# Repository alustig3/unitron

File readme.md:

# Unitron

<a href="https://certification.oshwa.org/us002571.html">
</img>
</a>

Unitron is a kitchen tool for working with important cooking units -- time, space, and mass -- using tactually-pleasing switches, knobs, and buttons, non-intrusive beeps, and exciting lights.

Unitron allows you to convert between common volume units (cups, ounces, tablespoons, teaspoons and milliliters). It can also convert from volume to mass (and vice-versa), taking into account the density of common cooking ingredients. This makes measuring ingredients for volume-based recipes with a kitchen scale a breeze. It also functions as a handy countdown timer!

Watch the demo video [here](https://vimeo.com/719658219).

Unitron was developed by Andy Lustig.

## Build Guide

### BOM

| Qty | Reference     | Description              | Value/MPN                                                                                                                                            |
| --- | ------------- | ------------------------ | ---------------------------------------------------------------------------------------------------------------------------------------------------- |
| 1   | BT2           | Battery Connector        | [2468](https://www.digikey.com/product-detail/en/keystone-electronics/2466/36-2466-ND/303815)                                                        |
| 1   | C1            | 0805 Capacitor           | 1µF                                                                                                                                                  |
| 1   | C2            | 0805 Capacitor           | 100nF                                                                                                                                                |
| 1   | C3            | 0805 Capacitor           | 10µF                                                                                                                                                 |
| 6   | D1-6          | Addressable RGB LED      | [WS2812B](https://cdn-shop.adafruit.com/datasheets/WS2812B.pdf)                                                                                      |
| 1   | D7            | Diode                    | [SM5817PL-TP](https://www.digikey.com/en/products/detail/micro-commercial-co/SM5817PL-TP/1793251)                                                    |
| 2   | D8, D9        | 0805 Indicator LED       | Red and Yellow                                                                                                                                       |
| 4   | H1-4          | Threaded Standoff        | [4207](https://www.adafruit.com/product/4207)                                                                                                        |
| 2   | J1, J3        | 1x8 male header          | [TSM-108-01-T-SV](https://www.digikey.com/en/products/detail/samtec-inc/TSM-108-01-T-SV/6679033)                                                     |
| 2   | J2, J4        | 1x8 female header        | [SSW-108-01-T-S](https://www.digikey.com/en/products/detail/samtec-inc/SSW-108-01-T-S/1112297)                                                       |
| 1   | LS1           | Buzzer                   | [PK-11N40PQ](https://www.digikey.com/en/products/detail/mallory-sonalert-products-inc/PK-11N40PQ/4996072?s=N4IgTCBcDaICwFYAcBaAjAZjmFA7AJiALoC%2BQA) |
| 21  | R1-18, R22-24 | 0805 Resistor            | 10KΩ                                                                                                                                                 |
| 3   | R19, R20, R21 | 0805 Resistor            | 2KΩ                                                                                                                                                  |
| 14  | S1-14         | Mechanical Key Switch    | [Gateron green](https://www.amazon.com/Gateron-KS-9-Mechanical-Type-Switch/dp/B07X3TH4DS?th=1)                                                       |
| 1   | SW1           | Small Toggle             | [B12AP](https://www.digikey.com/en/products/detail/nkk-switches/B12AP/379099)                                                                        |
| 1   | SW2           | Big Toggle               | [M2012EA2W13](https://www.digikey.com/en/products/detail/nkk-switches/M2012EA2W13/4509655)                                                           |
| 1   | SW3           | Rotary Encoder           | [PEC11R-4215F-S0024](https://www.digikey.com/en/products/detail/bourns-inc/PEC11R-4215F-S0024/4499665)                                               |
| 2   | U1, U2        | Yellow 4-Digit Display   | [LTC-4727JS](https://www.digikey.com/products/en?keywords=LTC-4727JS)                                                                                |
| 2   | U6, U7        | Red 4-Digit Display      | [LTC-4727JR](https://www.digikey.com/products/en?keywords=160-1551-5-nd)                                                                             |
| 2   | U3, U8        | 7-Segment Display Driver | [AS1115-BSST](https://www.digikey.com/products/en?keywords=AS1115-BSSTCT-ND)                                                                         |
| 1   | U4            | QT Py RP2040             | [4900](https://www.adafruit.com/product/4900)                                                                                                        |
| 1   | U5            | Battery Charging IC      | [MCP73831](https://www.digikey.com/en/products/detail/microchip-technology/MCP73831T-2ATI-OT/964303)                                                 |

<div style="">
  
</div>

### Additional Components
- A rechargeable 3.7V lithium polymer (LiPo) [battery](https://www.adafruit.com/product/1578)
- Threaded mounting [magnets](https://www.kjmagnetics.com/proddetail.asp?prod=MM-C-10)
- A satisfyingly knurled [metal knob](https://www.digikey.com/en/products/detail/kilo-international/OEDNI-63-4-7/5970335).
- Keycaps from WASD keycaps:
  - [number pad keycap set](https://www.wasdkeyboards.com/17-key-cherry-mx-number-pad-keycap-set.html) for the numbers (black, large font)
  - The number pad set comes with a 1x2 "0" keycap, but we want a [custom 1x1 "0" keycap](https://www.wasdkeyboards.com/custom-text-cherry-mx-keycaps.html) (R1 1x1, 26 font, center-center alignment)
  - [R1 1x1 keycaps](https://www.wasdkeyboards.com/row-1-size-1x1-cherry-mx-keycap.html) (sky blue, green, and orange)
- [Relegendable keycaps](https://www.adafruit.com/product/5039) are a good less expensive alternative.

## User Guide

### Component Diagram

### Turning it on!

The first step to using your Unitron is to turn it on with the smaller, right-most [On/Off switch](#diagram). When Unitron is on, the [LED panel](#diagram) and the red [Power indicator light](#diagram) will be lit up. Turn it off to save power.

### Switching Modes

Unitron has a [countdown timer mode](#timer) and [converter mode](#convert).
To **switch to modes**, click the [blue Mode button](#diagram).
Unitron will startup in the `start_mode` specified in your `settings.py` file (see [Modifying Unitron functionality](#modify)).
If the [blue Mode button](#diagram) is pressed down when turning on Unitron, it will startup in the opposite mode. 

### Countdown timer mode
To **set the timer**, use the number keys. To specify minutes and seconds, you can use the decimal key, e.g. 20.30 corresponds to 20 minutes and 30 seconds, while 20 corresponds to 20 seconds.

To **start** the timer, flip the [Toggle switch](#diagram). To **pause** the timer, flip the [Toggle switch](#diagram) again. The top, red row of the LED panel shows the time remaining, and the bottom orange row shows the original time requested.

To **clear** the timer, pause the timer (if necessary), then push the green [Clear button](#diagram).

As the timer counts down to 0, a bar of [Timer lights](#diagram) will progressively light up. When the timer reaches 0, it will beep three times.

### Converter mode
Unitron converts **from blinking to solid units** in the [Unit light](#diagram) row.

You can **enter the amount** of the **blinking "from"** units with the number keys. This will be shown in the [LED panel](#diagram). The corresponding amount in the **solid "to"** units will be shown in the other row of the [LED panel](#diagram).

You can **change units** using the [Knob](#diagram). Turning the knob changes the **blinking "from" units**. Turning the knob while holding it down changes the **solid "to" units**.

You can **swap** the "from" and "to" units with the [Toggle switch](#diagram).  If you find it difficult to hold down the Knob while turning it, you can use the Toggle switch to swap, turn the knob, then flip the Toggle switch back.

Conversions between volume and mass require knowing the density of the ingredient. You can **specify cooking ingredients** by holding down the orange [Ingredient button](#diagram) while turning the [Knob](#diagram). Note that the ingredient button only functions when the two units selected are mass and volume -- ingredient type does not matter when converting from mass to mass or volume to volume.

### Charging

Unitron is rechargeable. To charge it, plug a USB C cable into the [USB port](#diagram) at the top. The yellow charging indicator will be on while charging and will turn off when the battery is full.

### Placement

The back of Unitron has four strong magnets. It is meant to be placed on a metallic refrigerator.

###  Modifying Unitron functionality

Unitron uses [CircuitPython](https://learn.adafruit.com/welcome-to-circuitpython). 
You can modify the code it is running by connecting it to your computer via the [USB C port](#diagram) and mounting it as a disk drive.
Basic settings can be adjusted by editing the `settings.py` file.

**Change the mode that Unitron starts up in when turned on** by editing `start_mode`.

**Adjust the number of beeps** for when the timer expires by editing `beep_num`.

To **add new ingredients** to Unitron, modify `ingredients`. Specify the density in grams per teaspoon. You can try to measure these densities yourself, or you can trust the internet. Here's one [site](https://www.howmany.wiki/vw/) with information.

Make sure to **eject** Unitron before disconnecting.

### Updating 
#### CircuitPython
Connect Unitron to a computer via the [USB C port](#diagram).
To enter bootloader mode, hold down the `BOOT` button, and while continuing to hold it, press and release the `RST` button. Continue to hold the boot select button until the bootloader drive appears on your computer as `RPI-RP2`.
Download `adafruit-circuitpython-adafruit_qtpy_rp2040-en_US-9.0.4.uf2` file from the [release page](https://github.com/alustig3/unitron/releases) and drag it onto the bootloader drive. The `RPI-RP2` drive will disappear, and a new drive called `CIRCUITPY` will appear.

If you have trouble, take a look at the official CirtcuitPython installation instructions [here](https://learn.adafruit.com/welcome-to-circuitpython/installing-circuitpython).

#### Unitron Software
Connect Unitron to a computer via the [USB C port](#diagram).
It should appear as `CIRCUITPY`.
Download the latest software [release](https://github.com/alustig3/unitron/releases).
Unzip the download and copy the files onto the `CIRCUITPY` drive.

## License
[CERN Open Hardware Licence Version 2 - Permissive](https://github.com/alustig3/unitron/blob/main/LICENSE.txt)

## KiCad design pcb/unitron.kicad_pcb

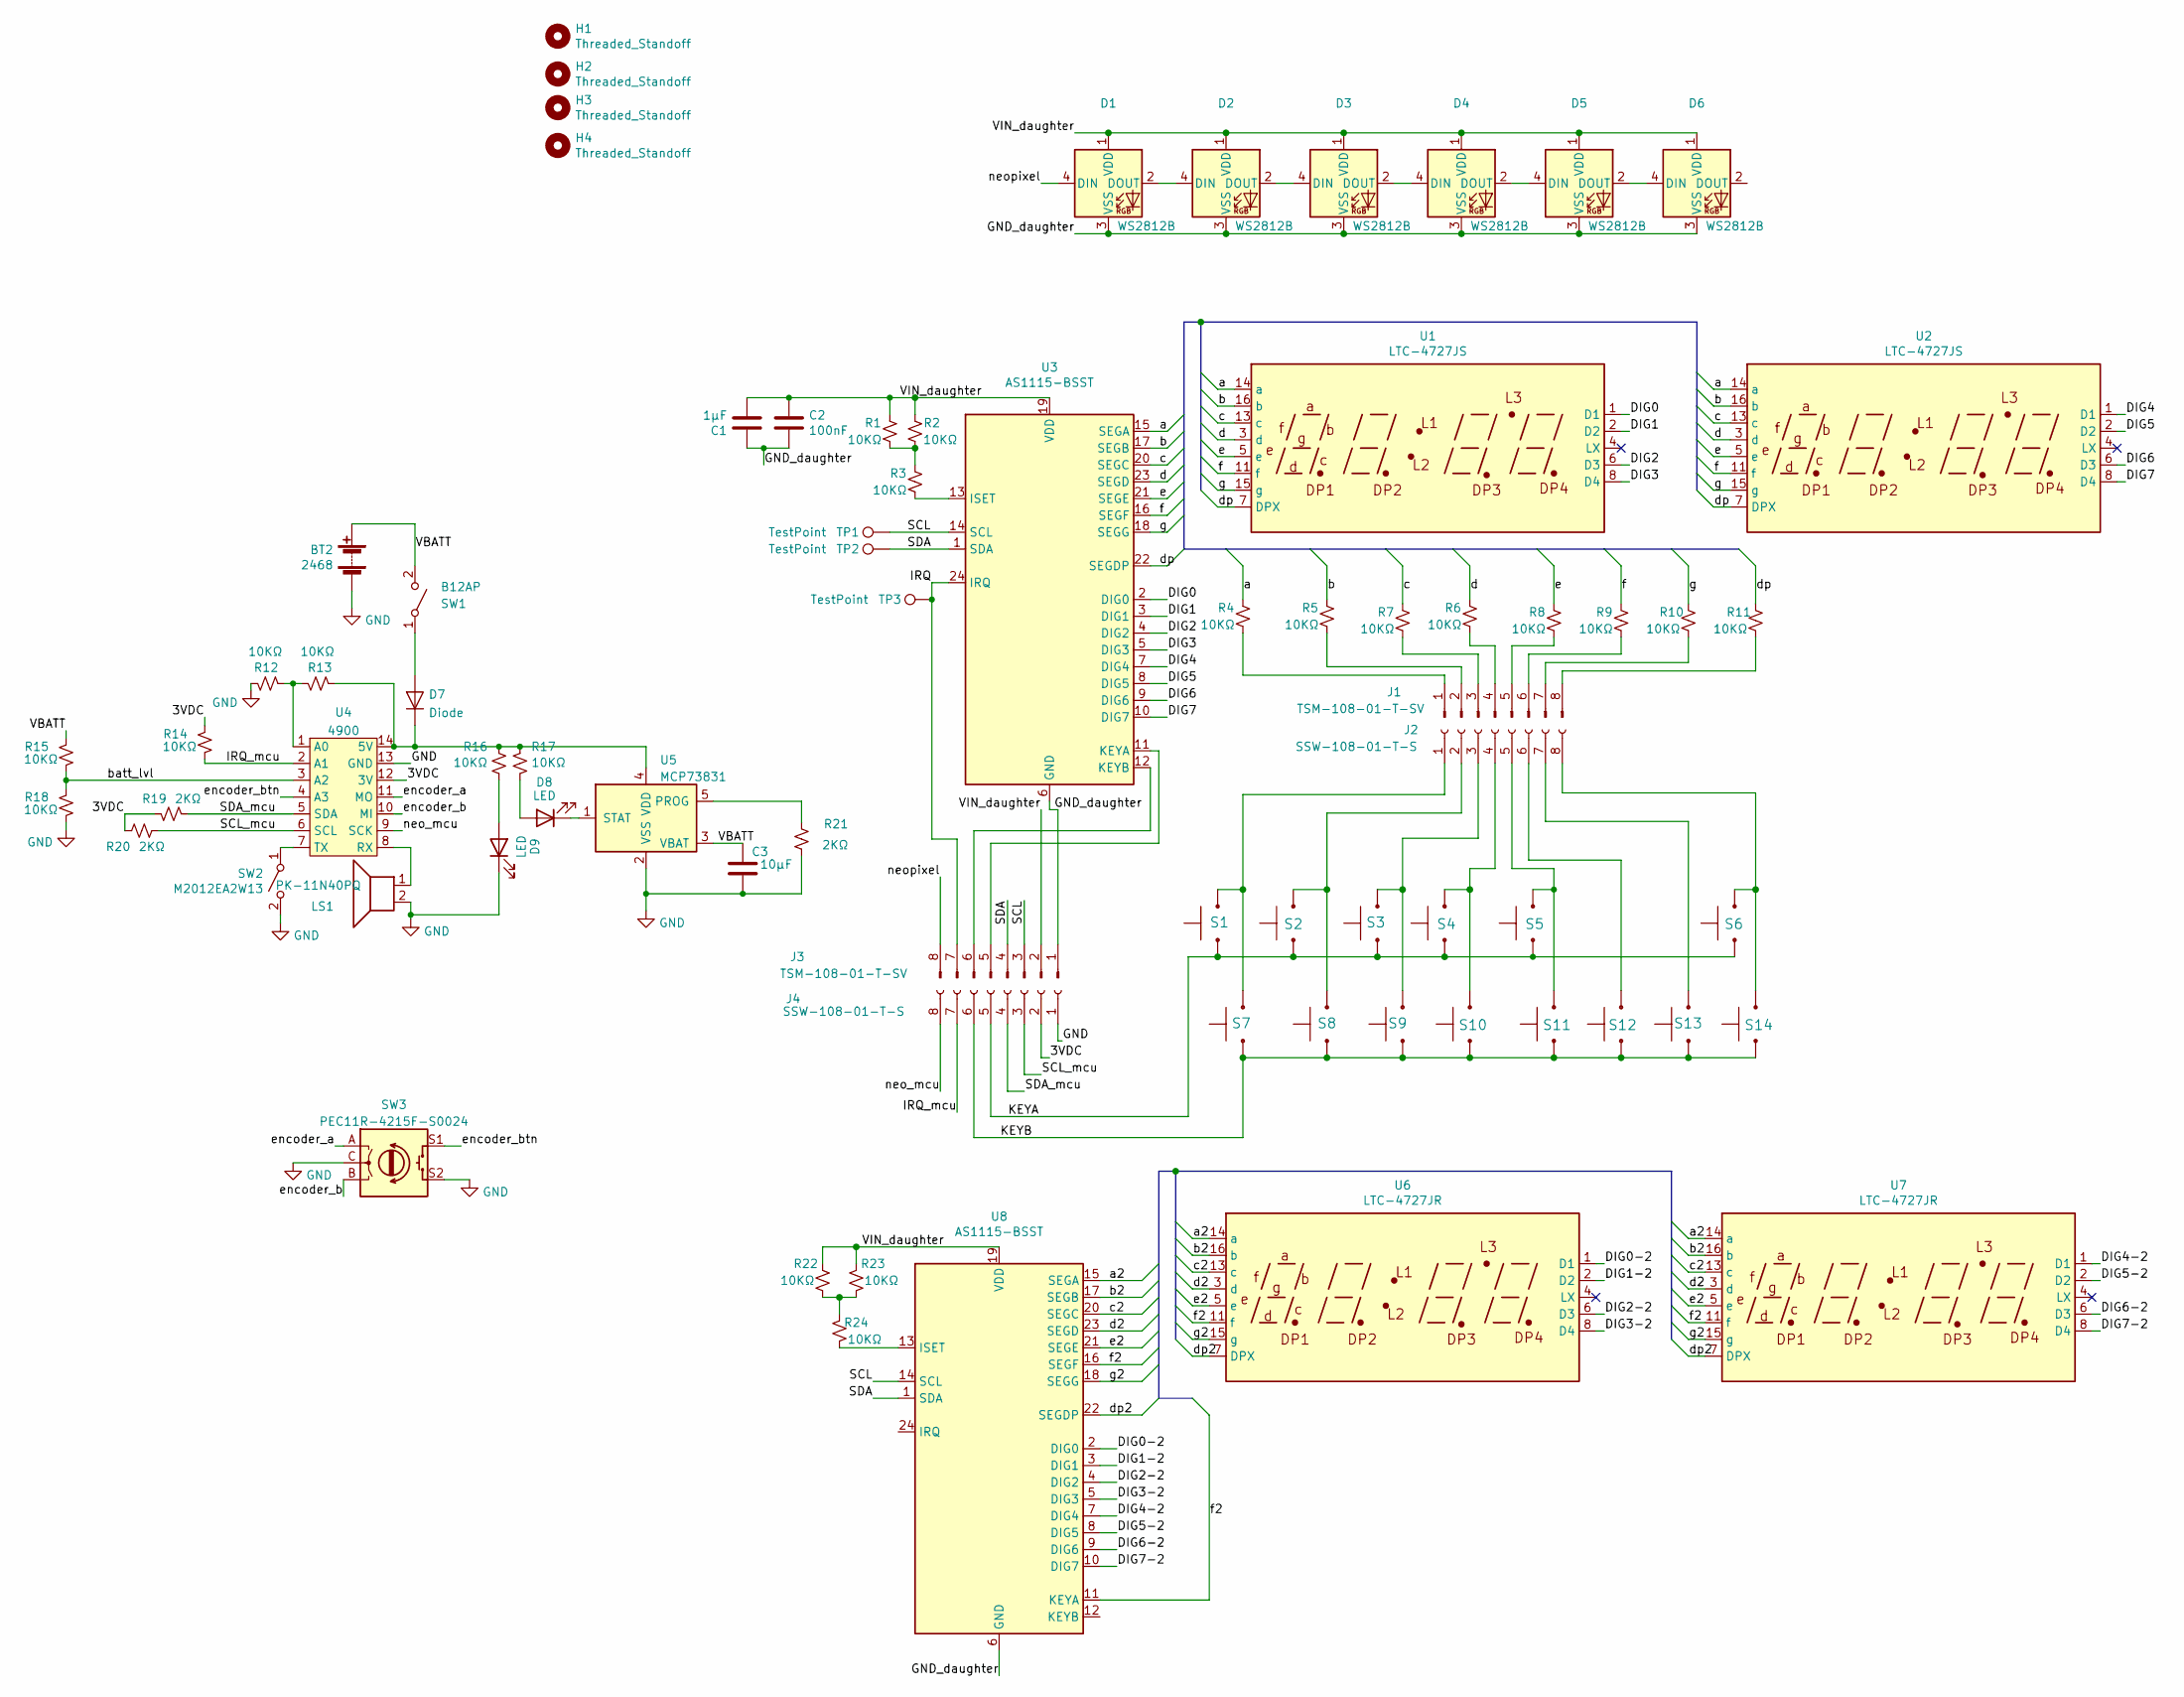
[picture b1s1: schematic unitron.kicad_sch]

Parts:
BT2: 2468; JST_PH_S2B-PH-SM4-TB_1x02-1MP_P2.00mm_Horizontal
C1: 1µF; C_0805_2012Metric
C2: 100nF; C_0805_2012Metric
C3: 10µF; C_0805_2012Metric
D1, D2, D3, D4, D5, D6: WS2812B; LED_WS2812B_PLCC4_5.0x5.0mm_P3.2mm
D7: Diode; D_SOD-123F
D8, D9: LED; LED_0805_2012Metric
H1, H2, H3, H4: Threaded_Standoff; standoff_nut
J1, J3: TSM-108-01-T-SV; PinSocket_1x08_P2.54mm_Vertical_SMD_Pin1Right
J2, J4: SSW-108-01-T-S; PinHeader_1x08_P2.54mm_Vertical
LS1: PK-11N40PQ; Buzzer_12x9.5RM7.6
R1, R2, R3, R4, R5, R6, R7, R8, R9, R10, R11, R12, R13, R14, R15, R16, R17, R18, R22, R23, R24: 10KΩ; R_0805_2012Metric
R19, R20, R21: 2KΩ; R_0805_2012Metric
S1, S2, S3, S4, S5, S6, S7, S8, S9, S10, S11, S12, S13, S14: Gateron green; SW_Cherry_MX_1.00u_PCB
SW1: B12AP; switch_toggle
SW2: M2012EA2W13; switch_nkk_reinforced_pc_pin
SW3: PEC11R-4215F-S0024; encoder_PEC11R
TP1, TP2, TP3: TestPoint; TestPoint_Pad_1.0x1.0mm
U1, U2: LTC-4727JS; LTC-4727
U3, U8: AS1115-BSST; QSOP-24_3.9x8.7mm_P0.635mm
U4: 4900; QT_Py
U5: MCP73831; SOT-23-5
U6, U7: LTC-4727JR; LTC-4727

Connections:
/3VDC: J4.2, R14.1, R19.2, R20.2, U4.12 (3V)
/DIG0: U1.1 (D1), U3.2 (DIG0)
/DIG0-2: U6.1 (D1), U8.2 (DIG0)
/DIG1: U1.2 (D2), U3.3 (DIG1)
/DIG1-2: U6.2 (D2), U8.3 (DIG1)
/DIG2: U1.6 (D3), U3.4 (DIG2)
/DIG2-2: U6.6 (D3), U8.4 (DIG2)
/DIG3: U1.8 (D4), U3.5 (DIG3)
/DIG3-2: U6.8 (D4), U8.5 (DIG3)
/DIG4: U2.1 (D1), U3.7 (DIG4)
/DIG4-2: U7.1 (D1), U8.7 (DIG4)
/DIG5: U2.2 (D2), U3.8 (DIG5)
/DIG5-2: U7.2 (D2), U8.8 (DIG5)
/DIG6: U2.6 (D3), U3.9 (DIG6)
/DIG6-2: U7.6 (D3), U8.9 (DIG6)
/DIG7: U2.8 (D4), U3.10 (DIG7)
/DIG7-2: U7.8 (D4), U8.10 (DIG7)
/GND_daughter: C1.1, C2.2, D1.3 (VSS), D2.3 (VSS), D3.3 (VSS), D4.3 (VSS), D5.3 (VSS), D6.3 (VSS), J3.1, U3.6 (GND), U8.6 (GND)
/IRQ: J3.7, TP3.1, U3.24 (IRQ)
/IRQ_mcu: J4.7, R14.2, U4.2 (A1)
/KEYA: J4.5, S1.1, S2.1, S3.1, S4.1, S5.1, S6.1
/KEYB: J4.6, S7.1, S8.1, S9.1, S10.1, S11.1, S12.1, S13.1, S14.1
/SCL: J3.3, TP1.1, U3.14 (SCL), U8.14 (SCL)
/SCL_mcu: J4.3, R20.1, U4.6 (SCL)
/SDA: J3.4, TP2.1, U3.1 (SDA), U8.1 (SDA)
/SDA_mcu: J4.4, R19.1, U4.5 (SDA)
/VBATT: BT2.1 (+), C3.1, R15.1, SW1.2 (B), U5.3 (VBAT)
/VIN_daughter: C1.2, C2.1, D1.1 (VDD), D2.1 (VDD), D3.1 (VDD), D4.1 (VDD), D5.1 (VDD), D6.1 (VDD), J3.2, R1.2, R2.2, R22.2, R23.2, U3.19 (VDD), U8.19 (VDD)
/a: R4.2, U1.14 (a), U2.14 (a), U3.15 (SEGA)
/a2: U6.14 (a), U7.14 (a), U8.15 (SEGA)
/b: R5.2, U1.16 (b), U2.16 (b), U3.17 (SEGB)
/b2: U6.16 (b), U7.16 (b), U8.17 (SEGB)
/batt_lvl: R15.2, R18.1, U4.3 (A2)
/c: R7.2, U1.13 (c), U2.13 (c), U3.20 (SEGC)
/c2: U6.13 (c), U7.13 (c), U8.20 (SEGC)
/d: R6.2, U1.3 (d), U2.3 (d), U3.23 (SEGD)
/d2: U6.3 (d), U7.3 (d), U8.23 (SEGD)
/dp: R11.2, U1.7 (DPX), U2.7 (DPX), U3.22 (SEGDP)
/dp2: U6.7 (DPX), U7.7 (DPX), U8.22 (SEGDP)
/e: R8.2, U1.5 (e), U2.5 (e), U3.21 (SEGE)
/e2: U6.5 (e), U7.5 (e), U8.21 (SEGE)
/encoder_a: SW3.A, U4.11 (MO)
/encoder_b: SW3.B, U4.10 (MI)
/encoder_btn: SW3.S1, U4.4 (A3)
/f: R9.2, U1.11 (f), U2.11 (f), U3.16 (SEGF)
/f2: U6.11 (f), U7.11 (f), U8.11 (KEYA), U8.16 (SEGF)
/g: R10.2, U1.15 (g), U2.15 (g), U3.18 (SEGG)
/g2: U6.15 (g), U7.15 (g), U8.18 (SEGG)
/neo_mcu: J4.8, U4.9 (SCK)
/neopixel: D1.4 (DIN), J3.8
GND: BT2.2 (-), C3.2, D9.1 (K), J4.1, LS1.2, R12.2, R18.2, R21.1, SW2.2 (B), SW3.C, SW3.S2, U4.13 (GND), U5.2 (VSS)
unnamed: D1.2 (DOUT), D2.4 (DIN)
unnamed: D2.2 (DOUT), D3.4 (DIN)
unnamed: D3.2 (DOUT), D4.4 (DIN)
unnamed: D4.2 (DOUT), D5.4 (DIN)
unnamed: D5.2 (DOUT), D6.4 (DIN)
unnamed: D7.1 (K), R13.1, R16.1, R17.1, U4.14 (5V), U5.4 (VDD)
unnamed: D7.2 (A), SW1.1 (A)
unnamed: D8.1 (K), U5.1 (STAT)
unnamed: D8.2 (A), R17.2
unnamed: D9.2 (A), R16.2
unnamed: J1.1, R4.1
unnamed: J1.2, R5.1
unnamed: J1.3, R7.1
unnamed: J1.4, R6.1
unnamed: J1.5, R8.1
unnamed: J1.6, R9.1
unnamed: J1.7, R10.1
unnamed: J1.8, R11.1
unnamed: J2.1, S1.2, S7.2
unnamed: J2.2, S2.2, S8.2
unnamed: J2.3, S3.2, S9.2
unnamed: J2.4, S4.2, S10.2
unnamed: J2.5, S5.2, S11.2
unnamed: J2.6, S12.2
unnamed: J2.7, S13.2
unnamed: J2.8, S6.2, S14.2
unnamed: J3.5, U3.11 (KEYA)
unnamed: J3.6, U3.12 (KEYB)
unnamed: LS1.1, U4.8 (RX)
unnamed: R1.1, R2.1, R3.2
unnamed: R3.1, U3.13 (ISET)
unnamed: R12.1, R13.2, U4.1 (A0)
unnamed: R21.2, U5.5 (PROG)
unnamed: R22.1, R23.1, R24.2
unnamed: R24.1, U8.13 (ISET)
unnamed: SW2.1 (A), U4.7 (TX)

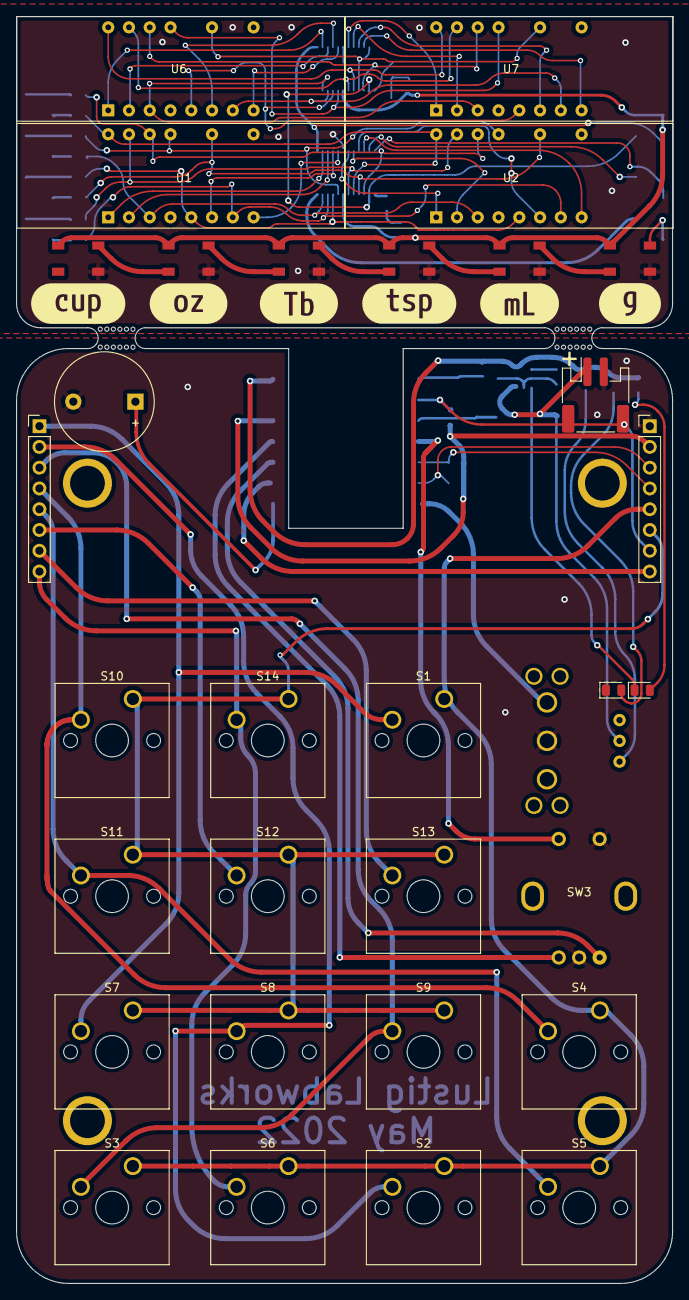
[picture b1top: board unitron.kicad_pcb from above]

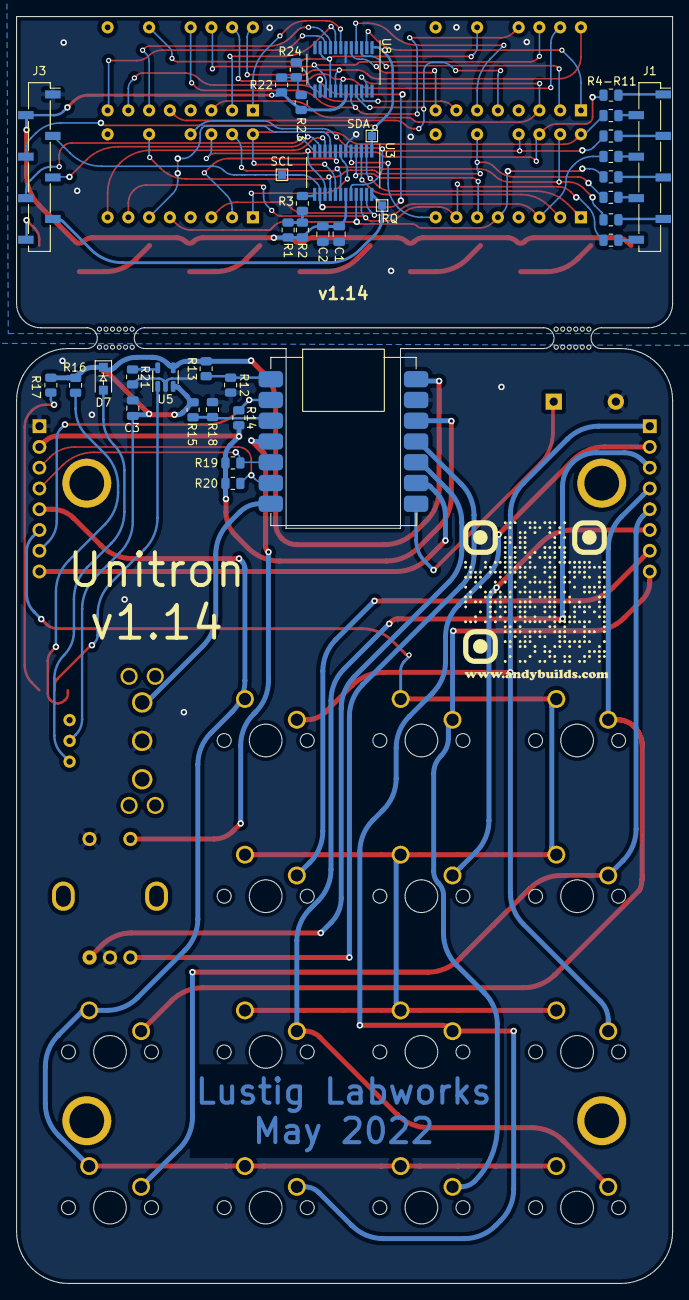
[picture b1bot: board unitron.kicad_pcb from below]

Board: 2 copper layers, 80.3 x 155.0 mm, 82 parts (37 on the bottom side), 87 nets.

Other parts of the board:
MB*: VAL**; mouse-bite-2.54mm-slot-long
MB*#2: VAL**; mouse-bite-2.54mm-slot-long
kibuzzard-6260D7DE: G***; kibuzzard-6260D7DE
kibuzzard-6260D82F: G***; kibuzzard-6260D82F
kibuzzard-6260D796: G***; kibuzzard-6260D796
kibuzzard-6260D857: G***; kibuzzard-6260D857
kibuzzard-6260D976: G***; kibuzzard-6260D976
kibuzzard-6260DA5E: G***; kibuzzard-6260DA5E

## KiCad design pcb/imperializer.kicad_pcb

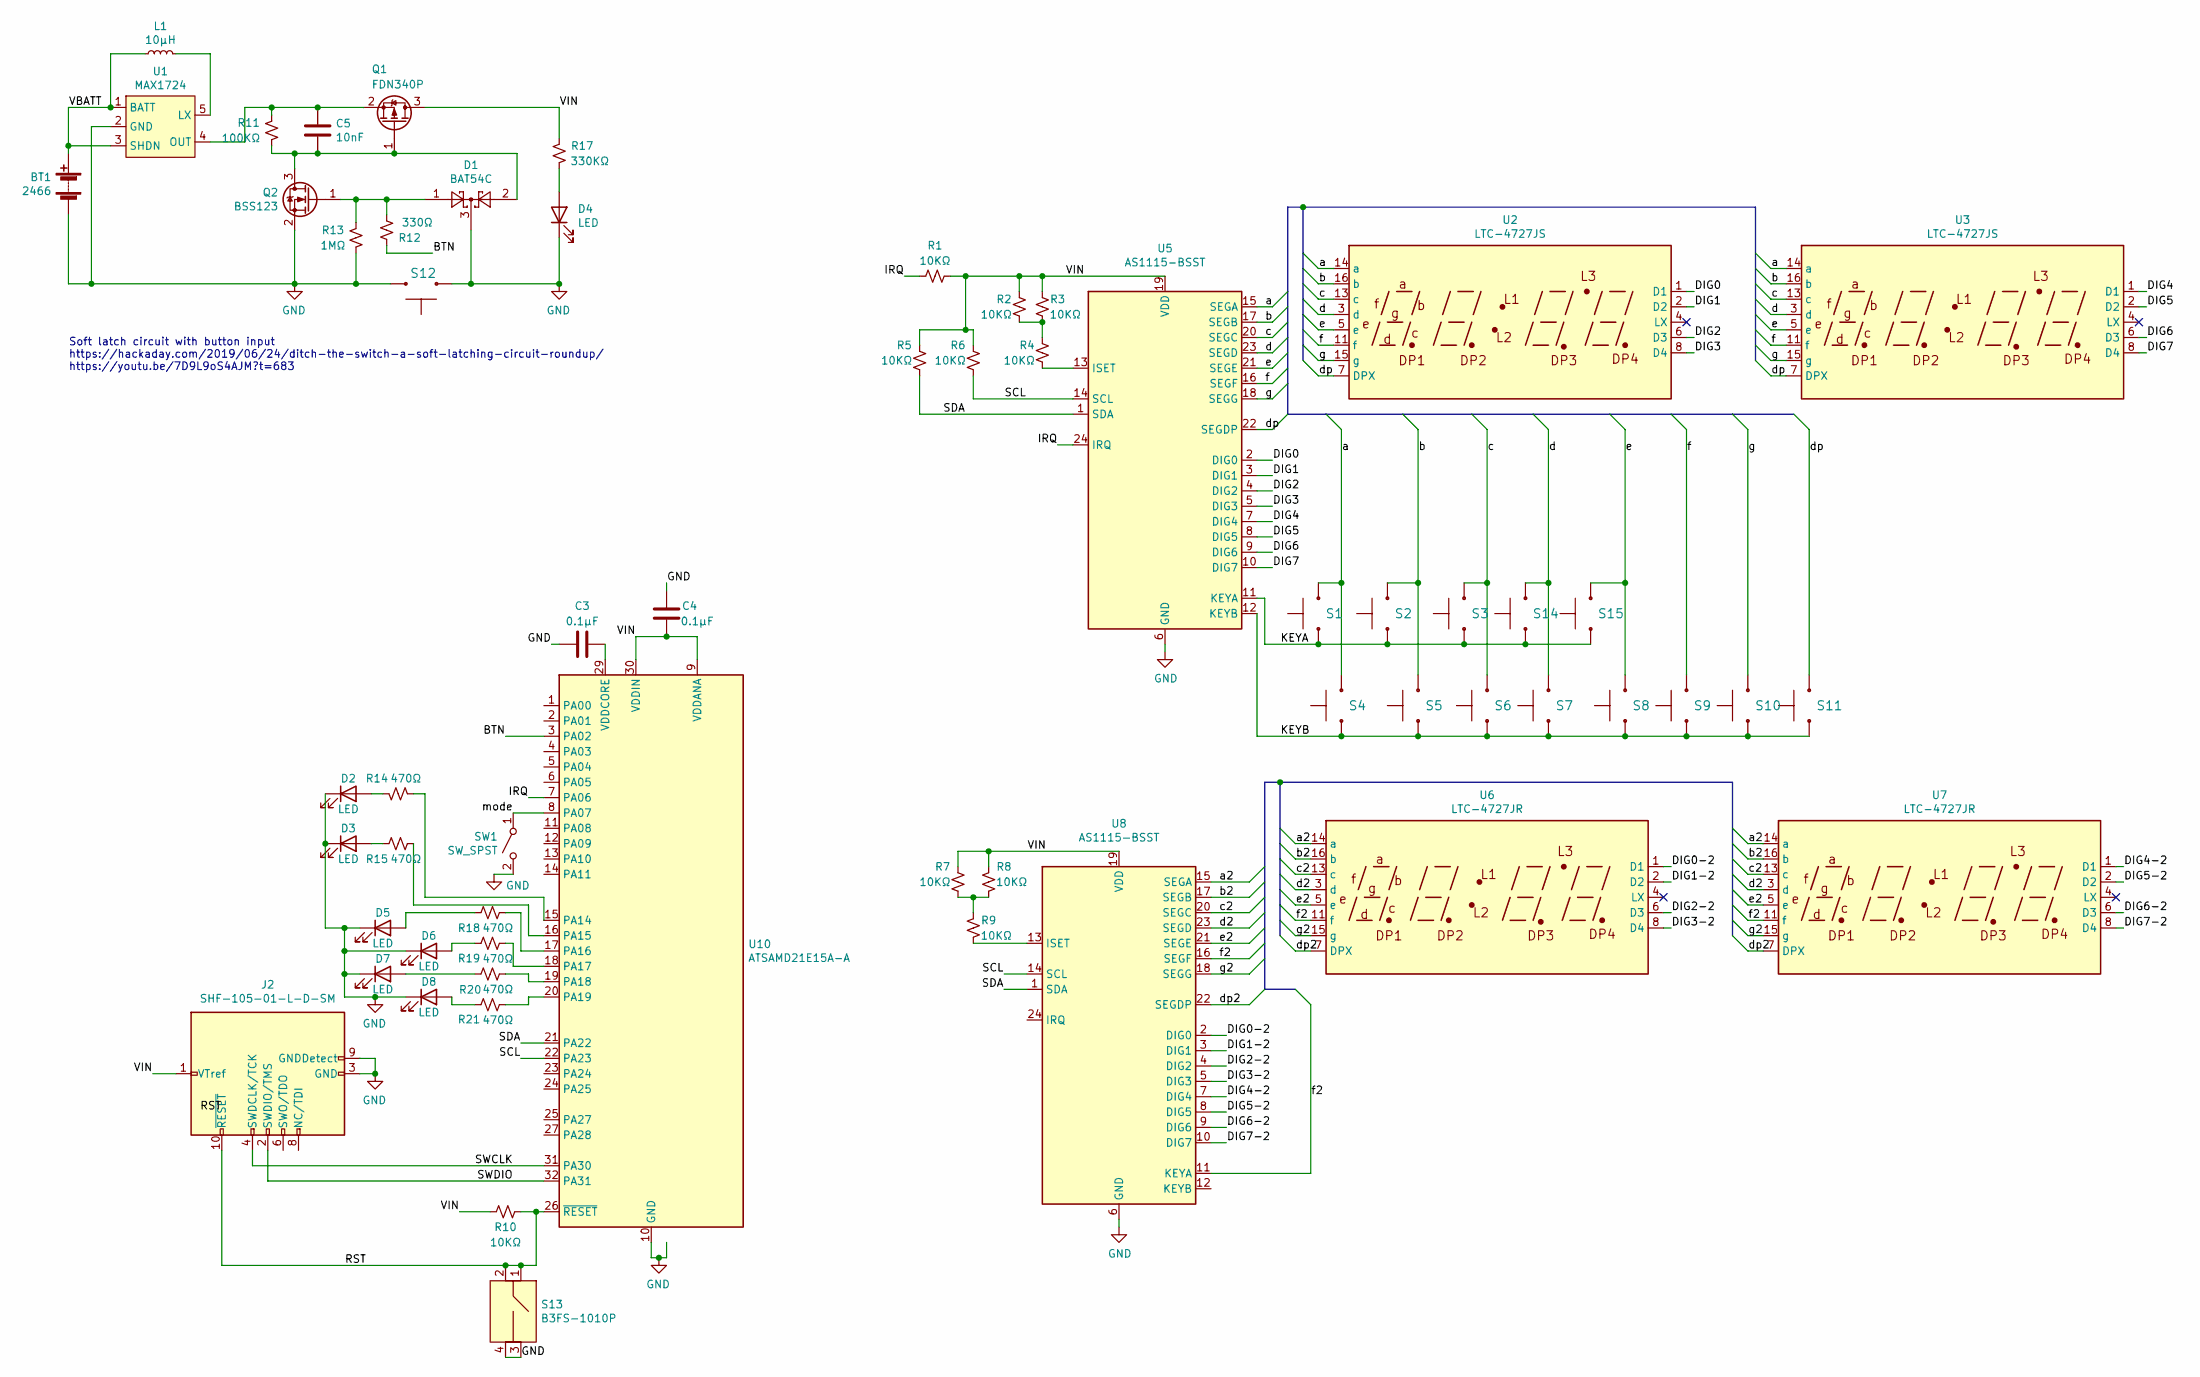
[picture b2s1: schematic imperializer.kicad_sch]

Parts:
BT1: 2466; BatteryHolder_Keystone_2466_1xAAA
C3, C4: 0.1µF; C_0805_2012Metric
C5: 10nF; C_0805_2012Metric
D1: BAT54C; SOT-23
D2, D3, D4, D5, D6, D7, D8: LED; LED_0805_2012Metric
J2: SHF-105-01-L-D-SM; SWD_2x5_socket
L1: 10µH; L_0805_2012Metric
Q1: FDN340P; SOT-23
Q2: BSS123; SOT-23
R1, R2, R3, R4, R5, R6, R7, R8, R9, R10: 10KΩ; R_0805_2012Metric
R11: 100KΩ; R_0805_2012Metric
R12: 330Ω; R_0805_2012Metric
R13: 1MΩ; R_0805_2012Metric
R14, R15, R18, R19, R20, R21: 470Ω; R_0805_2012Metric
R17: 330KΩ; R_0805_2012Metric
S1, S2, S4, S5, S6, S7, S8, S9, S10, S11, S12, S14, S15: Gateron Blue; SW_Cherry_MX_1.00u_PCB
S3: Gateron Blue; SW_Cherry_MX_2.00u_PCB
S13: B3FS-1010P; 6mm_tactile_smd
SW1: SW_SPST; B12AP
U1: MAX1724; SOT-23-5
U2, U3: LTC-4727JS; LTC-4727
U5, U8: AS1115-BSST; QSOP-24_3.9x8.7mm_P0.635mm
U6, U7: LTC-4727JR; LTC-4727
U10: ATSAMD21E15A-A; TQFP-32_7x7mm_P0.8mm

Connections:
/BTN: R12.1, U10.3 (PA02)
/DIG0: U2.1 (D1), U5.2 (DIG0)
/DIG0-2: U6.1 (D1), U8.2 (DIG0)
/DIG1: U2.2 (D2), U5.3 (DIG1)
/DIG1-2: U6.2 (D2), U8.3 (DIG1)
/DIG2: U2.6 (D3), U5.4 (DIG2)
/DIG2-2: U6.6 (D3), U8.4 (DIG2)
/DIG3: U2.8 (D4), U5.5 (DIG3)
/DIG3-2: U6.8 (D4), U8.5 (DIG3)
/DIG4: U3.1 (D1), U5.7 (DIG4)
/DIG4-2: U7.1 (D1), U8.7 (DIG4)
/DIG5: U3.2 (D2), U5.8 (DIG5)
/DIG5-2: U7.2 (D2), U8.8 (DIG5)
/DIG6: U3.6 (D3), U5.9 (DIG6)
/DIG6-2: U7.6 (D3), U8.9 (DIG6)
/DIG7: U3.8 (D4), U5.10 (DIG7)
/DIG7-2: U7.8 (D4), U8.10 (DIG7)
/IRQ: R1.2, U5.24 (IRQ), U10.7 (PA06)
/KEYA: S1.1, S2.1, S3.1, S14.1, S15.1, U5.11 (KEYA)
/KEYB: S4.1, S5.1, S6.1, S7.1, S8.1, S9.1, S10.1, S11.1, U5.12 (KEYB)
/RST: J2.10 (~RESET~), R10.1, S13.1 (in1), S13.2 (in2), U10.26 (~RESET)
/SCL: R6.1, U5.14 (SCL), U8.14 (SCL), U10.22 (PA23)
/SDA: R5.1, U5.1 (SDA), U8.1 (SDA), U10.21 (PA22)
/SWCLK: J2.4 (SWDCLK/TCK), U10.31 (PA30)
/SWDIO: J2.2 (SWDIO/TMS), U10.32 (PA31)
/VBATT: BT1.1 (+), L1.1, U1.1 (BATT), U1.3 (SHDN)
/VIN: C4.1, J2.1 (VTref), Q1.3 (D), R1.1, R2.2, R3.2, R5.2, R6.2, R7.2, R8.2, R10.2, R17.1, U5.19 (VDD), U8.19 (VDD), U10.9 (VDDANA), U10.30 (VDDIN)
/a: S1.2, S4.2, U2.14 (a), U3.14 (a), U5.15 (SEGA)
/a2: U6.14 (a), U7.14 (a), U8.15 (SEGA)
/b: S2.2, S5.2, U2.16 (b), U3.16 (b), U5.17 (SEGB)
/b2: U6.16 (b), U7.16 (b), U8.17 (SEGB)
/c: S3.2, S6.2, U2.13 (c), U3.13 (c), U5.20 (SEGC)
/c2: U6.13 (c), U7.13 (c), U8.20 (SEGC)
/d: S7.2, S14.2, U2.3 (d), U3.3 (d), U5.23 (SEGD)
/d2: U6.3 (d), U7.3 (d), U8.23 (SEGD)
/dp: S11.2, U2.7 (DPX), U3.7 (DPX), U5.22 (SEGDP)
/dp2: U6.7 (DPX), U7.7 (DPX), U8.22 (SEGDP)
/e: S8.2, S15.2, U2.5 (e), U3.5 (e), U5.21 (SEGE)
/e2: U6.5 (e), U7.5 (e), U8.21 (SEGE)
/f: S9.2, U2.11 (f), U3.11 (f), U5.16 (SEGF)
/f2: U6.11 (f), U7.11 (f), U8.11 (KEYA), U8.16 (SEGF)
/g: S10.2, U2.15 (g), U3.15 (g), U5.18 (SEGG)
/g2: U6.15 (g), U7.15 (g), U8.18 (SEGG)
/mode: SW1.1 (A), U10.8 (PA07)
GND: BT1.2 (-), C3.1, C4.2, D1.3, D2.1 (K), D3.1 (K), D4.1 (K), D5.1 (K), D6.1 (K), D7.1 (K), D8.1 (K), J2.3 (GND), J2.5 (GND), J2.9 (GNDDetect), Q2.2 (S), R13.1, S12.1, S12.2, S13.3 (out1), S13.4 (out2), SW1.2 (B), U1.2 (GND), U5.6 (GND), U8.6 (GND), U10.10 (GND), U10.28 (GND)
unnamed: C3.2, U10.29 (VDDCORE)
unnamed: C5.1, Q1.2 (S), R11.2, U1.4 (OUT)
unnamed: C5.2, D1.2, Q1.1 (G), Q2.3 (D), R11.1
unnamed: D1.1, Q2.1 (G), R12.2, R13.2
unnamed: D2.2 (A), R14.2
unnamed: D3.2 (A), R15.2
unnamed: D4.2 (A), R17.2
unnamed: D5.2 (A), R18.2
unnamed: D6.2 (A), R19.2
unnamed: D7.2 (A), R20.2
unnamed: D8.2 (A), R21.2
unnamed: L1.2, U1.5 (LX)
unnamed: R2.1, R3.1, R4.2
unnamed: R4.1, U5.13 (ISET)
unnamed: R7.1, R8.1, R9.2
unnamed: R9.1, U8.13 (ISET)
unnamed: R18.1, U10.17 (PA16)
unnamed: R19.1, U10.18 (PA17)
unnamed: R20.1, U10.19 (PA18)
unnamed: R21.1, U10.20 (PA19)
unnamed: R14.1, U10.15 (PA14)
unnamed: R15.1, U10.16 (PA15)

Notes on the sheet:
Soft latch circuit with button input https://hackaday.com/2019/06/24/ditch-the-switch-a-soft-latching-circuit-roundup/ https://youtu.be/7D9L9oS4AJM?t=683

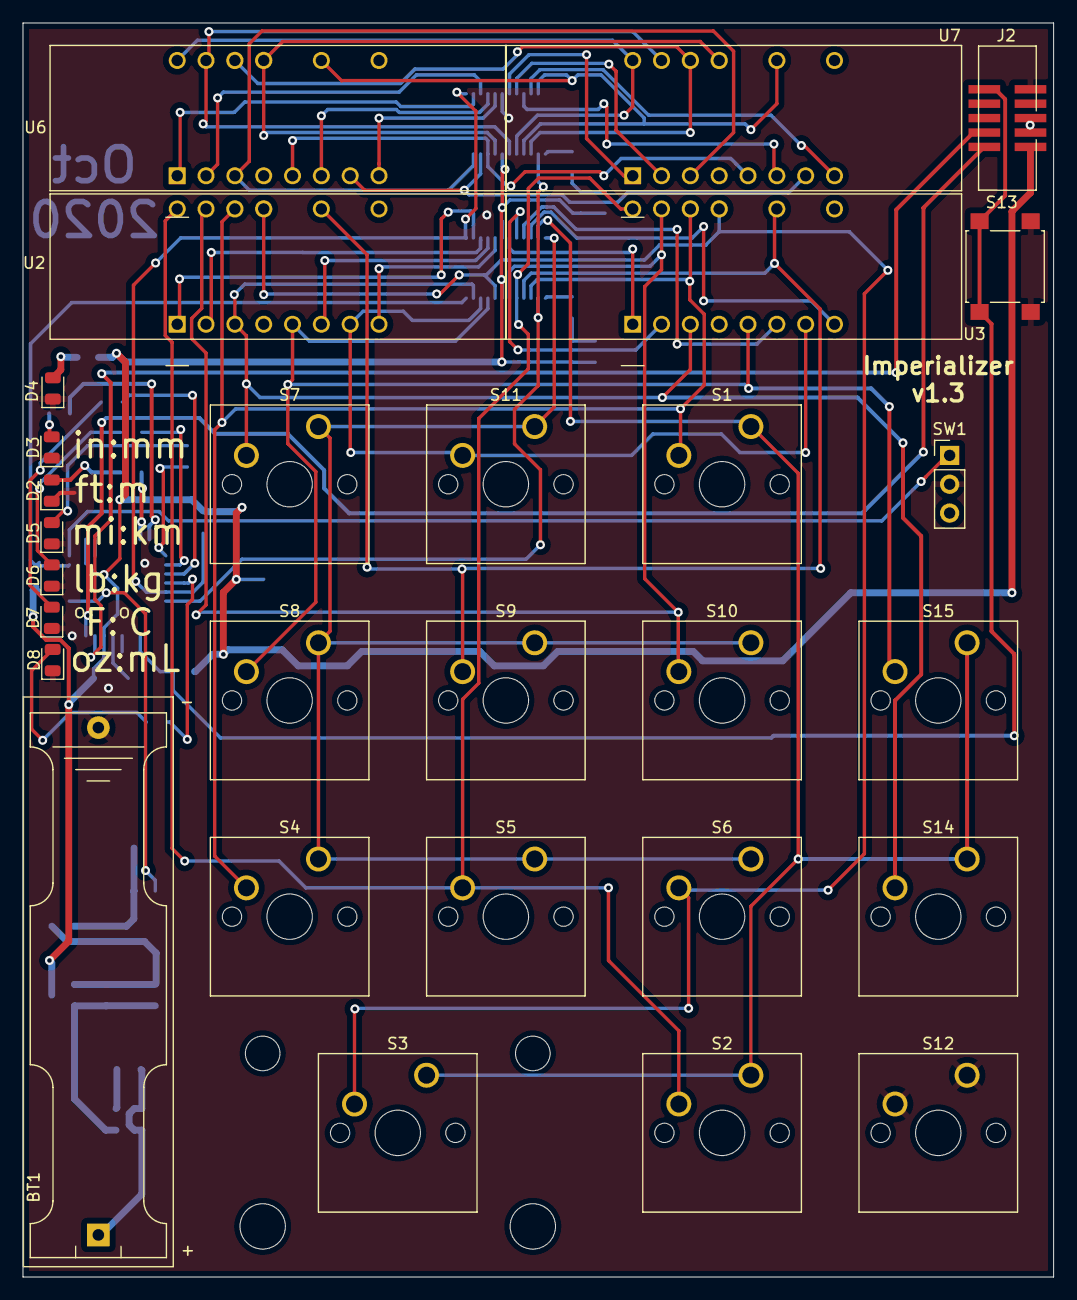
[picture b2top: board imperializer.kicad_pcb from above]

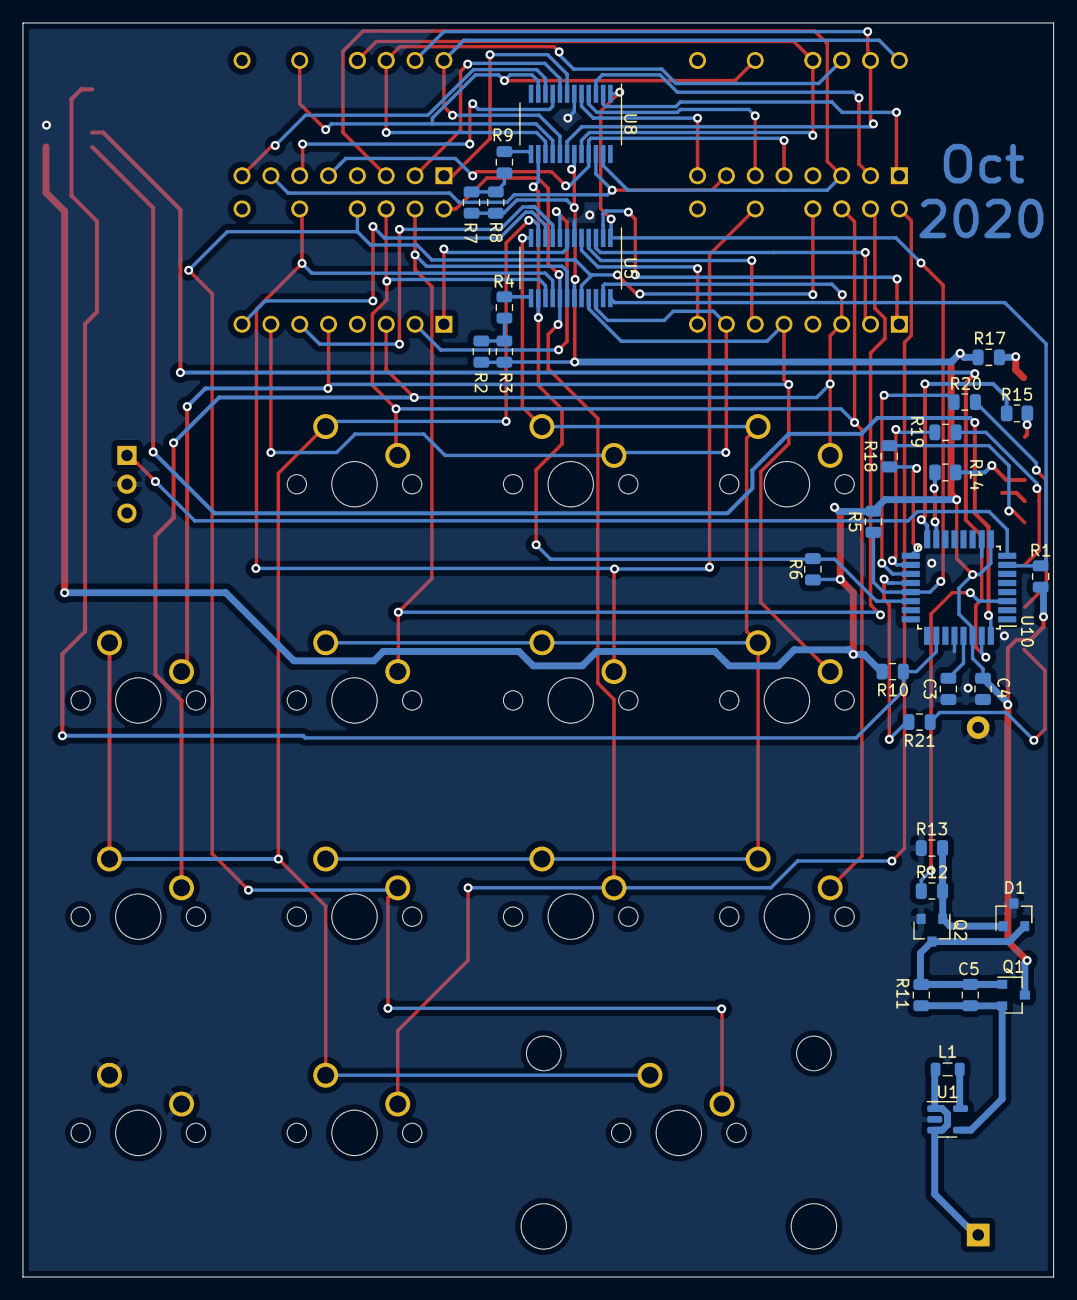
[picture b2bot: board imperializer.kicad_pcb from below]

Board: 2 copper layers, 90.8 x 110.5 mm, 60 parts (31 on the bottom side), 67 nets.

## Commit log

2020-05-08 first version of pcb. 32u4, toggle switch 1 row/8 digits display
2020-06-06 keys, mode toggle switch, and 2 displays working
2020-06-06 added datasheets
2020-06-06 increments only down downstroke. switch moves the number between left and right side.
2020-06-06 got rid of leading zeros
2020-06-07 display now show number of key that is pressed
2020-06-07 live conversion!!!
2020-06-08 Input blinks, output is bright.
2020-06-08 result with 1 decimal place working
2020-06-09 decimal input works now!
2020-06-09 adjustable decimal precision now works
2020-06-09 cleaned up code, remove pow()
2020-06-10 working with 2 drivers, 4 displays
2020-06-11 4 displays working. conversion code still needs work. internal zeros and leading zeros still need work
2020-06-11 can now lead with zero
2020-06-11 internal decimal 0's now working. double click "." to clear
2020-06-11 fixes 0 being inserted when keys are quickly pressed in succession.
2020-06-13 cleaned up code
2020-06-21 slower clock I2C clock speed make startup more reliable.
2020-08-02 pcb v1.1
2020-08-24 more reliable startup. added more conversions.
2020-08-27 Added bootloader for SAMD21
2020-09-15 pcb v1.2
    switched to bare SAMD21
    added USB-C connector
    added 4 conversion selection LEDs
    added on/off button with soft latch circuit
    rearranged toggles switch and battery holders
2020-09-17 Kicad update
    updated to kicad 5.99 nightly. There is now a new file format
2020-10-18 add platformio project
2020-10-18 v1.2 features added
    soft latch works. press to turn on, hold to turn off
    can cycle through conversion modes. corresponding indicator LEDs will light up
    can specify number of decimals and if number is negative.
    sends keypresses to computer as keyboard device
2020-10-19 Modified to work with esp32 feather
2020-10-26 pcb v1.3
2020-10-27 New library format
2020-10-27 library update
2020-10-30 Instant startup and auto shutdown
    - New upload configuration. Removed bootloader and crystal configuration. Lose use native USB communication, but much faster startup
    - added auto shutdown after 30s of inactivity
2020-11-05 added clear and negative button functionality
2020-11-06 Fixed bug where negative sign wasn't showing properly for numbers less than 1
2020-11-06 Added 2 more ft:m and oz:ml conversions
2020-11-30 update pcb library
2021-02-02 pcb v1.4
2021-02-13 dotstar and eeprom working
2021-02-14 PCB v1.5
2021-02-24 working software
    - corresponding leds light up when units change
    - last used unit is saved and retrieved from EEPROM
2021-03-02 cleanup
2021-03-02 moved datasheets
2021-03-02 added mechanical files
2021-03-02 added gdb commands for blackmagic probe
2021-03-02 added .step file to mechanical
2021-03-02 update .gitignore some more
2021-03-02 changed library submodule to https address
2021-03-07 clear line animation
    lines sweep left then right on input when clear button is used
2021-03-07 only shown digits are dashed then cleared
2021-03-09 pcb v1.6
2021-03-20 updated to use 10 dotstars instead of 12
2021-03-20 add erase to makefile
2021-03-20 set brightness to 4
2021-10-30 pcb v1.7
2021-11-21 unitron v 1.8
    changed to QT PY and added lipo battery charging circuit
2021-12-13 pcb v1.9
2022-01-10 v1.10
    shift as1115 label closer to pin 1
    remove "1" label from km neopixel
    make IRQ trace and via larger.
    change i2c pullups from 10k to 2k
    added diodes to keyscan traces so multiple buttons can simultaneously be pressed
    make cutout for different qt py
2022-03-19 v 1.11
2022-03-23 pcb v1.12
2022-04-25 pcb v1.13
2022-05-03 working software for v1.12
2022-05-05 working software for v1.13
2022-05-15 pcb v1.14
2022-05-15 clean up and testing sleep
2022-05-16 reorganize code
2022-05-16 more cleanup
2022-05-21 starting to add timer
2022-05-22 basic timer working with progress bar
2022-05-30 inputs and outputs are now strings
    added "-" clearing
    put constrains on input digits and output decimal places
2022-05-31 simplified changing unit
2022-06-02 pixels are now part of physical class
2022-06-04 clock interface working with timer
2022-06-04 toggling while tick will now pause the timer
2022-06-06 startup "unitron" and more letters
2022-07-12 starts up in timer mode
    updated libraries as well
2022-08-29 clean up directory for sharing
2022-08-29 added rough readme
2022-08-29 condensed BOM values
2022-10-22 library updates
2022-11-03 new settings.py file
    - added some new ingredients
    - added letter "y"
    - number of beeps and startup mode now adjustable in a settings.py file
2022-11-03 Updated readme with User Guide
    Thank you Kristin!
2022-11-03 forgot component diagram
2022-11-03 added information for updating
2022-11-08 readme updates
2023-01-01 code cleanup
2023-01-01 recall last used ingredient from memory
2023-01-01 remove boot.py renaming
2023-01-01 Unitron will startup opposite of its default mode if the mode button is pressed when Unitron is switched on
2023-01-01 A details about starting up in opposite mode
2023-01-02 fix crash that happened if ingredient button pressed while in countdown mode
2023-01-02 changed countdown timer display text
2023-02-18 fix broken link
2023-10-30 add license
2023-10-30 add to readme link to license
2023-11-15 Add OSHWA certification mark
2024-05-10 temp
2024-05-10 update libraries for CircuitPython 9
2024-05-10 fix out of index bug that occurs during very first startup
2024-05-10 updated update instructions
